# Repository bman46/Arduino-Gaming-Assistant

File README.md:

# Arduino Gaming Assistant:

A windows service application that communicates with an arduino and sends temperature information about GPU Temp and CS:GO kills, Arduino recives data through serial and displays it on a OLED screen. This was formerly known as ArduinoTemp.
## Setup:
  #### Arduino:
  - Verify that [MultiLCD Library](https://github.com/stanleyhuangyc/MultiLCD) is installed
  - Upload Arduino TempDisplay.ino file to arduino.
  - Connect I2C OLED display power to corresoponding power connections
  - Connect SCL to A5
  - Connect SDA to A4
  - When powered on/restarted, LCD Should dislay: Starting..
    - if it doesnt, comment the``` LCD_SSD1306 lcd; ``` line and uncomment another one that corresponds to your screen type.
  #### Install on Windows PC:
  - [Download/Install Visual Studio 2017](https://www.visualstudio.com/downloads/)
  - Open ArduinoTemp.sln with Visual Studio
  - Go to Build>Build Solution
  - On the Windows Start menu or Start screen, open the Visual Studio 2017 folder, then run Developer Command Prompt as admin. 
  - Navigate to build folder using pushd (Build Output Directory) 
  - Type in to console:``` installutil ArduinoTemp.exe ```
    -Should say "The transacted install had completed." and "The Commit phase completed successfully."
  - Open services.msc and find ArduinoTemp
  - Start by right clicking on it and click start
   #### Uninstall/Update on Windows PC:
  - On the Windows Start menu or Start screen, open the Visual Studio 2017 folder, then run Developer Command Prompt as admin. 
  - Type in to console: ``` installutil /u ArduinoTemp.exe ```
  - Open services.msc and verify ArduinoTemp is no longer there.
  - If updating, follow the install instructions after completing the uninstall.
  #### Add .cfg Files to CS:GO:
  - Download the gamestate_integration_ArduinoTemp.cfg
  - Place the file in the CS:GO cfg folder:
    - for example: ```D:\Steam\steamapps\common\Counter-Strike Global Offensive\csgo\cfg\```
  - CS:GO Support thanks to the [CSGSI Library](https://github.com/rakijah/CSGSI)
  - ##### Note: This should not get you VAC banned as it is supported by valve. However, dont go messing around in other folders unless you know what your doing. [Read More Here](https://developer.valvesoftware.com/wiki/Counter-Strike:_Global_Offensive_Game_State_Integration)

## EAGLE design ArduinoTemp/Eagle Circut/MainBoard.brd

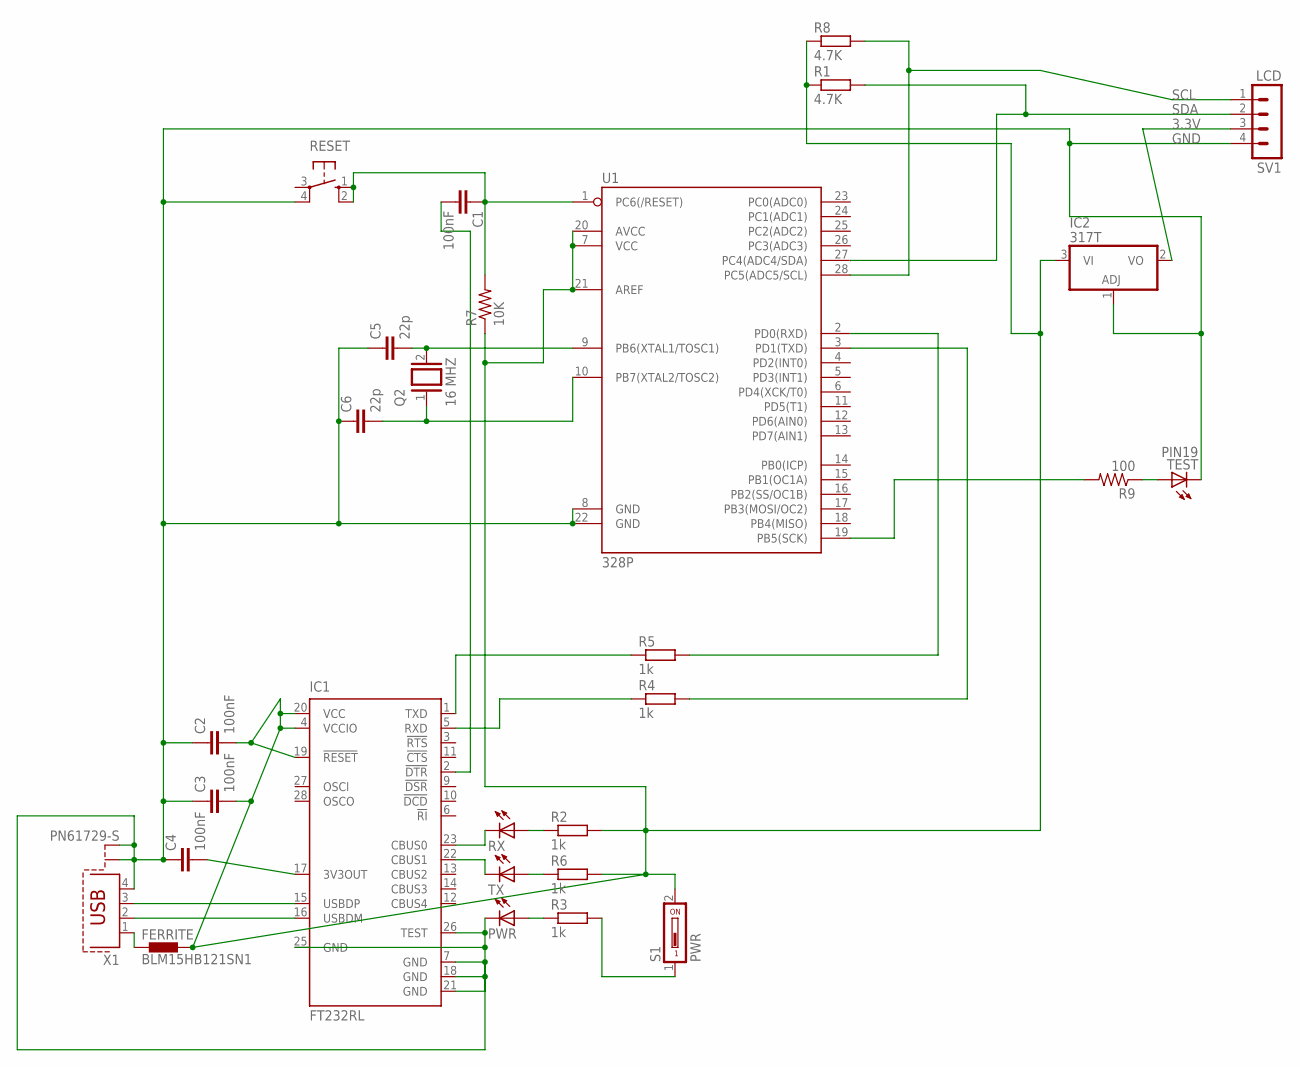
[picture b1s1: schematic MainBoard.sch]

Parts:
C1, C2, C3, C4: 100nF; C025-025X050
C5, C6: 22p; C025-025X050
FERRITE: BLM15HB121SN1; 0402
IC1: FT232RL; SSOP28
IC2: 317T; TO220H
PWR: LED5MM
Q2: 16 MHZ; QS
R1, R8: 4.7K; 0207/10
R2, R3, R4, R5, R6: 1k; 0207/10
R7: 10K; 0207/10
R9: 100; 0207/10
RESET: 10-XX; B3F-10XX
RX: LED5MM
S1: PWR; DS-01
SV1: LCD; MA04-1
TEST: PIN19; LED5MM
TX: LED5MM
U1: 328P; DIP28
X1: PN61729-S

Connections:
3.3V: IC2.2 (VO), SV1.3
GND: C2.1, C3.1, C4.1, C5.1, C6.1, IC1.7 (GND), IC1.18 (GND), IC1.21 (GND), IC1.25 (GND), IC1.26 (TEST), IC2.1 (ADJ), PWR.K (C), RESET.4 (P1), SV1.4, TEST.K (C), U1.8 (GND), U1.22 (GND), X1.4, X1.S1, X1.S2
unnamed: IC1.1 (TXD), R5.1
unnamed: IC1.16 (USBDM), X1.2
unnamed: IC1.15 (USBDP), X1.3
unnamed: C2.2, C3.2, FERRITE.2, IC1.4 (VCCIO), IC1.19 (!RESET), IC1.20 (VCC), IC2.3 (VI), R1.1, R2.2, R6.2, R7.1, R8.1, S1.2, U1.7 (VCC), U1.20 (AVCC), U1.21 (AREF)
unnamed: C4.2, IC1.17 (3V3OUT)
unnamed: FERRITE.1, X1.1
unnamed: R9.1, TEST.A
unnamed: IC1.5 (RXD), R4.1
unnamed: R5.2, U1.2 (PD0(RXD))
unnamed: R4.2, U1.3 (PD1(TXD))
unnamed: IC1.23 (CBUS0), RX.K (C)
unnamed: R2.1, RX.A
unnamed: IC1.22 (CBUS1), TX.K (C)
unnamed: R6.1, TX.A
unnamed: PWR.A, R3.1
unnamed: R3.2, S1.1
unnamed: C1.2, IC1.2 (!DTR)
unnamed: R9.2, U1.19 (PB5(SCK))
unnamed: C5.2, Q2.2, U1.9 (PB6(XTAL1/TOSC1))
unnamed: C6.2, Q2.1, U1.10 (PB7(XTAL2/TOSC2))
PIN1: C1.1, R7.2, RESET.1 (S), RESET.2 (S1), U1.1 (PC6(/RESET))
SCL: R8.2, SV1.1, U1.28 (PC5(ADC5/SCL))
SDA: R1.2, SV1.2, U1.27 (PC4(ADC4/SDA))

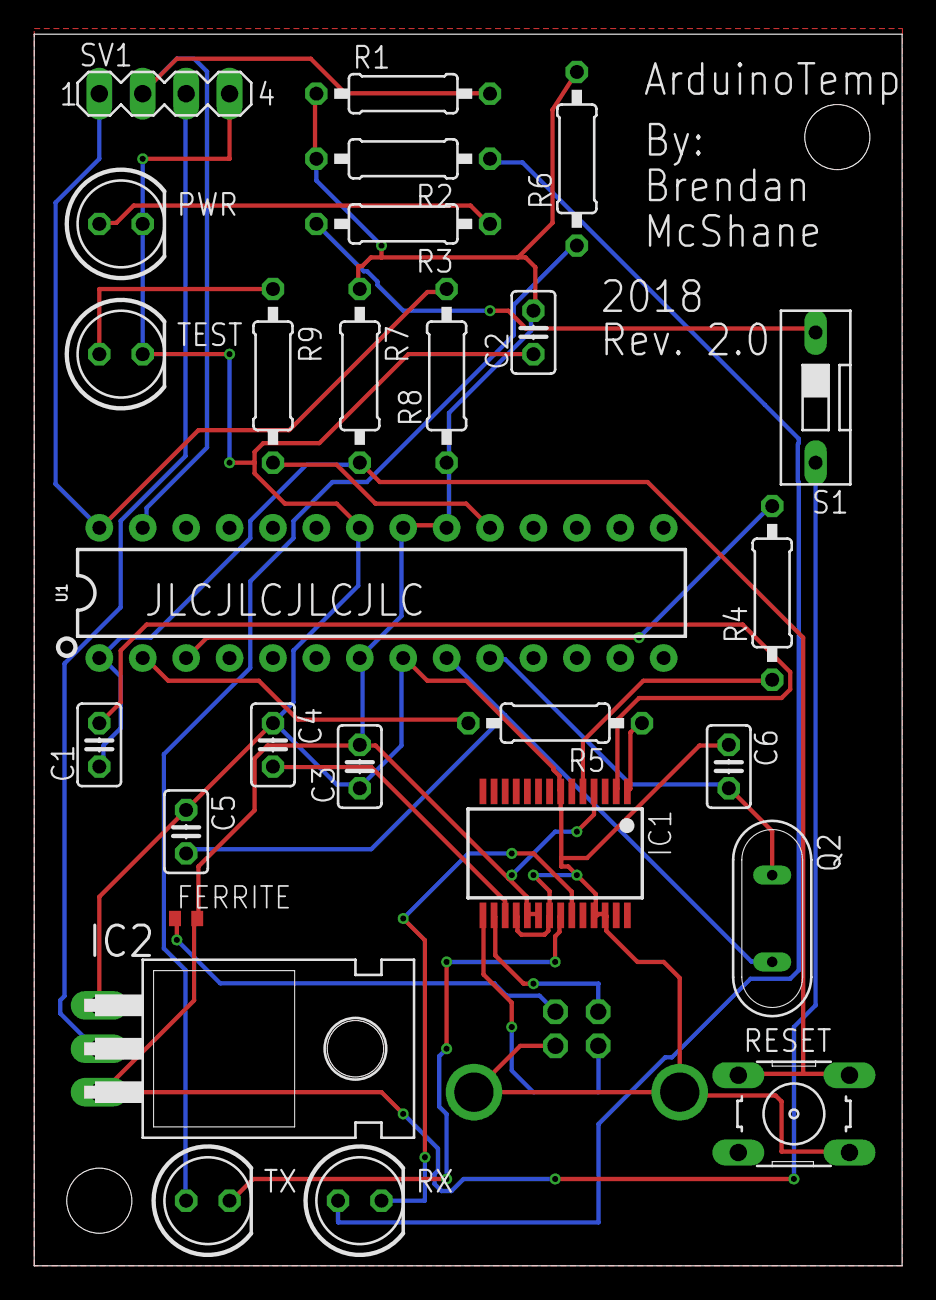
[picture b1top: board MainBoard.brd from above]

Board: 2 copper layers, 50.8 x 72.1 mm, 28 parts (1 on the bottom side), 25 nets.

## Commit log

2018-02-19 Visual Studio Files
2018-02-19 Readme Created
2018-02-19 Arduino Code Changes
2018-02-19 Small Changes...
2018-02-20 directory changes
2018-03-18 4 digit output fix
    if the computer sends data when the screen is refreshing, it causes the Arduino to display the last temp and the updated temp. Example: (temp: 5958 C) when it should be (temp: 58 C)
2018-03-18 efficiency
    Faster screen loading times
2018-03-20 Fix bugs
2018-05-29 Add CS:GO Support
2018-05-29 CS:GO Support
2018-05-29 CS:GO Integration
2018-08-29 Add time
2018-08-29 add 3d print
2019-07-16 Use 12Hr time instead of 24hr time
2019-07-16 make 12 hr format
2019-08-02 remove files
2019-08-02 add new files
2019-08-02 upload files
2019-08-02 add dll to release
2019-08-02 add debug folder
2019-08-02 reconnect after disconnect.
2022-06-22 Bump Newtonsoft.Json from 11.0.2 to 13.0.1 in /ArduinoTemp
    Bumps [Newtonsoft.Json](https://github.com/JamesNK/Newtonsoft.Json) from 11.0.2 to 13.0.1.
    - [Release notes](https://github.com/JamesNK/Newtonsoft.Json/releases)
    - [Commits](https://github.com/JamesNK/Newtonsoft.Json/compare/11.0.2...13.0.1)
    ---
    updated-dependencies:
    - dependency-name: Newtonsoft.Json
2022-12-08 Bump Newtonsoft.Json from 11.0.2 to 13.0.2 in /ArduinoTemp
    Bumps [Newtonsoft.Json](https://github.com/JamesNK/Newtonsoft.Json) from 11.0.2 to 13.0.2.
    - [Release notes](https://github.com/JamesNK/Newtonsoft.Json/releases)
    - [Commits](https://github.com/JamesNK/Newtonsoft.Json/compare/11.0.2...13.0.2)
    ---
    updated-dependencies:
    - dependency-name: Newtonsoft.Json

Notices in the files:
parts and their libraries:
SparkFun-IC-Microcontroller: Licensing: Creative Commons ShareAlike 4.0 International - https://creativecommons.org/licenses/by-sa/4.0
